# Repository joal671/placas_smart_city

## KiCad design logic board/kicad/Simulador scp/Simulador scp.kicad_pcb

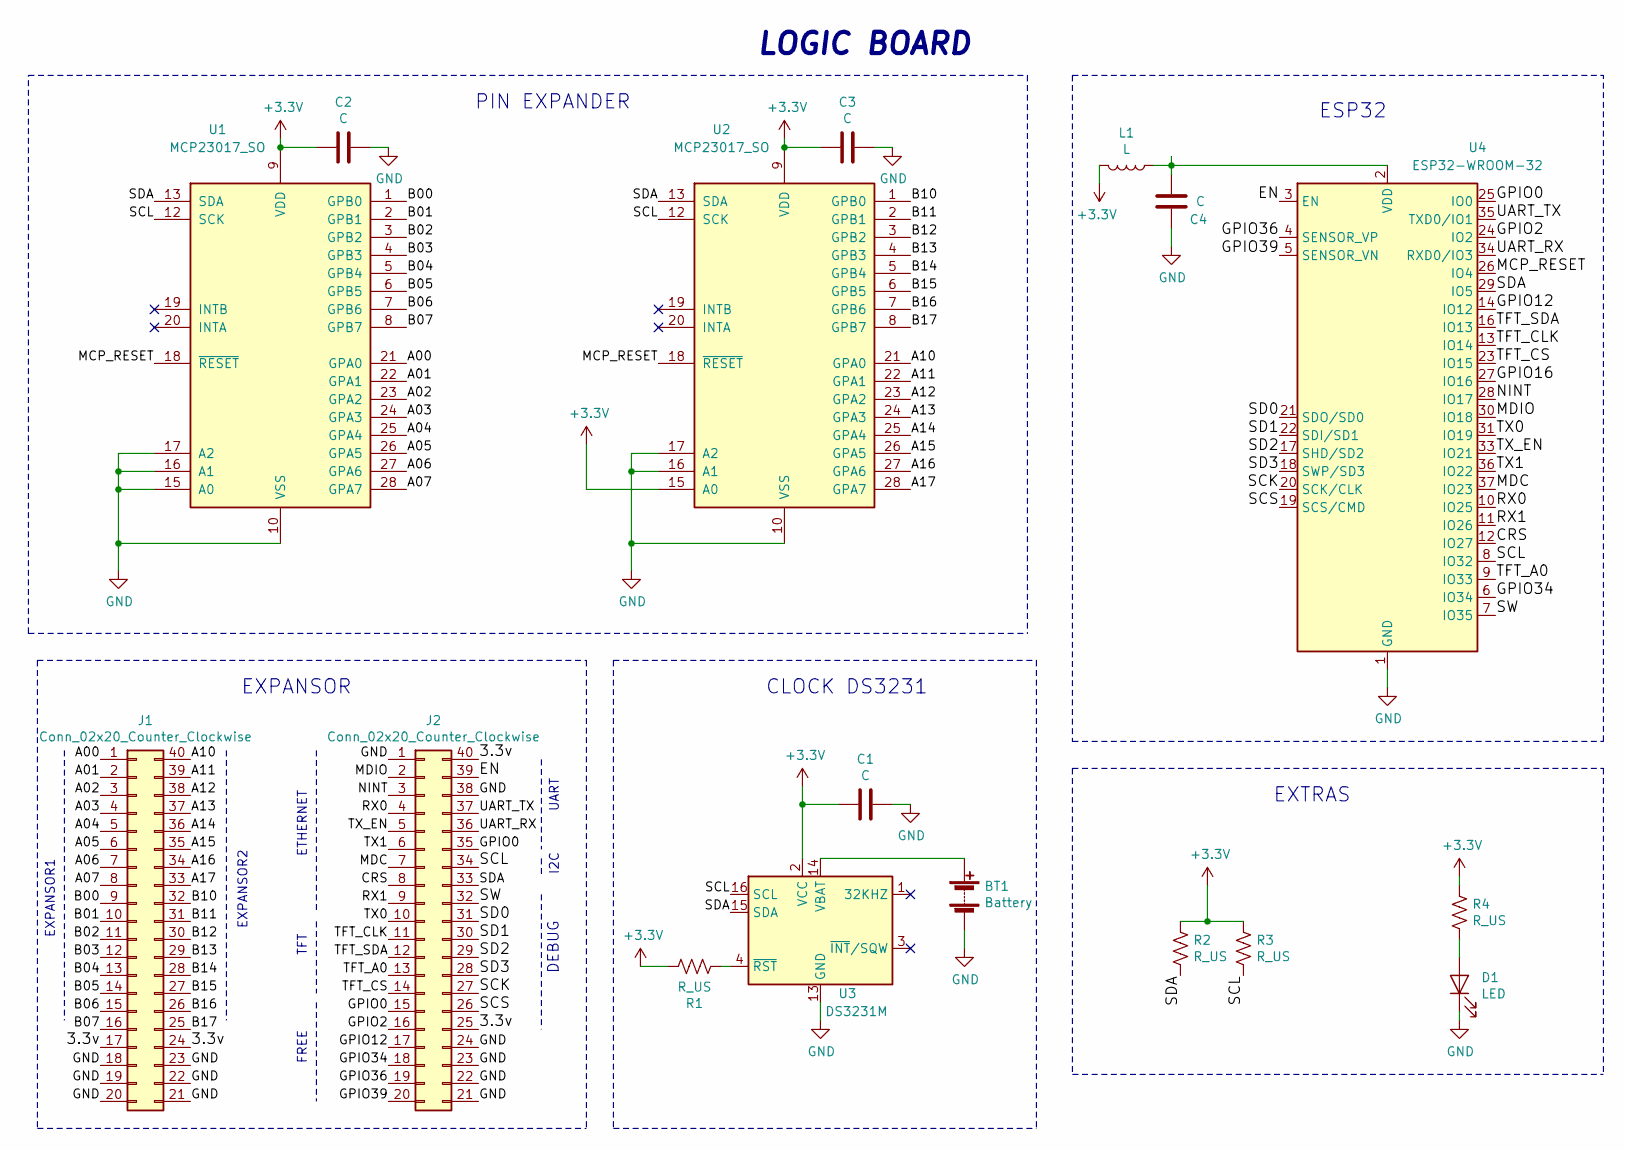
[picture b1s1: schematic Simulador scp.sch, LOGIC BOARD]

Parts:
BT1: Battery; BatteryHolder_Keystone_1060_1x2032
C1, C2, C3, C4: C; C_0805_2012Metric
D1: LED; LED_0805_2012Metric
J1, J2: Conn_02x20_Counter_Clockwise; Header 2x20-2.54mm
L1: L; L_0805_2012Metric
R1, R2, R3, R4: R_US; R_0805_2012Metric
U1, U2: MCP23017_SO; SOIC-28W_7.5x17.9mm_P1.27mm
U3: DS3231M; SOIC-16W_7.5x10.3mm_P1.27mm
U4: ESP32-WROOM-32

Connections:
+3V3: C1.2, C2.2, C3.2, L1.2, R1.1, R2.1, R3.1, R4.1, U1.9 (VDD), U2.9 (VDD), U2.15 (A0), U3.2 (VCC)
/3.3v: J1.17, J1.24, J2.25, J2.40
/A00: J1.1, U1.21 (GPA0)
/A01: J1.2, U1.22 (GPA1)
/A02: J1.3, U1.23 (GPA2)
/A03: J1.4, U1.24 (GPA3)
/A04: J1.5, U1.25 (GPA4)
/A05: J1.6, U1.26 (GPA5)
/A06: J1.7, U1.27 (GPA6)
/A07: J1.8, U1.28 (GPA7)
/A10: J1.40, U2.21 (GPA0)
/A11: J1.39, U2.22 (GPA1)
/A12: J1.38, U2.23 (GPA2)
/A13: J1.37, U2.24 (GPA3)
/A14: J1.36, U2.25 (GPA4)
/A15: J1.35, U2.26 (GPA5)
/A16: J1.34, U2.27 (GPA6)
/A17: J1.33, U2.28 (GPA7)
/B00: J1.9, U1.1 (GPB0)
/B01: J1.10, U1.2 (GPB1)
/B02: J1.11, U1.3 (GPB2)
/B03: J1.12, U1.4 (GPB3)
/B04: J1.13, U1.5 (GPB4)
/B05: J1.14, U1.6 (GPB5)
/B06: J1.15, U1.7 (GPB6)
/B07: J1.16, U1.8 (GPB7)
/B10: J1.32, U2.1 (GPB0)
/B11: J1.31, U2.2 (GPB1)
/B12: J1.30, U2.3 (GPB2)
/B13: J1.29, U2.4 (GPB3)
/B14: J1.28, U2.5 (GPB4)
/B15: J1.27, U2.6 (GPB5)
/B16: J1.26, U2.7 (GPB6)
/B17: J1.25, U2.8 (GPB7)
/CRS: J2.8, U4.12 (IO27)
/EN: J2.39, U4.3 (EN)
/GPIO0: J2.15, J2.35, U4.25 (IO0)
/GPIO2: J2.16, U4.24 (IO2)
/GPIO12: J2.17, U4.14 (IO12)
/GPIO16: U4.27 (IO16)
/GPIO34: J2.18, U4.6 (IO34)
/GPIO36: J2.19, U4.4 (SENSOR_VP)
/GPIO39: J2.20, U4.5 (SENSOR_VN)
/MCP_RESET: U1.18 (~RESET~), U2.18 (~RESET~), U4.26 (IO4)
/MDC: J2.7, U4.37 (IO23)
/MDIO: J2.2, U4.30 (IO18)
/NINT: J2.3, U4.28 (IO17)
/RX0: J2.4, U4.10 (IO25)
/RX1: J2.9, U4.11 (IO26)
/SCK: J2.27, U4.20 (SCK/CLK)
/SCL: J2.34, R3.2, U1.12 (SCK), U2.12 (SCK), U3.16 (SCL), U4.8 (IO32)
/SCS: J2.26, U4.19 (SCS/CMD)
/SD0: J2.31, U4.21 (SDO/SD0)
/SD1: J2.30, U4.22 (SDI/SD1)
/SD2: J2.29, U4.17 (SHD/SD2)
/SD3: J2.28, U4.18 (SWP/SD3)
/SDA: J2.33, R2.2, U1.13 (SDA), U2.13 (SDA), U3.15 (SDA), U4.29 (IO5)
/SW: J2.32, U4.7 (IO35)
/TFT_A0: J2.13, U4.9 (IO33)
/TFT_CLK: J2.11, U4.13 (IO14)
/TFT_CS: J2.14, U4.23 (IO15)
/TFT_SDA: J2.12, U4.16 (IO13)
/TX0: J2.10, U4.31 (IO19)
/TX1: J2.6, U4.36 (IO22)
/TX_EN: J2.5, U4.33 (IO21)
/UART_RX: J2.36, U4.34 (RXD0/IO3)
/UART_TX: J2.37, U4.35 (TXD0/IO1)
GND: BT1.2 (-), C1.1, C2.1, C3.1, C4.1, D1.1 (K), J1.18, J1.19, J1.20, J1.21, J1.22, J1.23, J2.1, J2.21, J2.22, J2.23, J2.24, J2.38, U1.10 (VSS), U1.15 (A0), U1.16 (A1), U1.17 (A2), U2.10 (VSS), U2.16 (A1), U2.17 (A2), U3.5 (GND), U3.6 (GND), U3.7 (GND), U3.8 (GND), U3.9 (GND), U3.10 (GND), U3.11 (GND), U3.12 (GND), U3.13 (GND), U4.1 (GND), U4.15 (GND), U4.38 (GND), U4.39 (GND)
unnamed: BT1.1 (+), U3.14 (VBAT)
unnamed: C4.2, L1.1, U4.2 (VDD)
unnamed: D1.2 (A), R4.2
unnamed: R1.2, U3.4 (~RST)

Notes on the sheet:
PIN EXPANDER
ESP32
EXPANSOR
CLOCK DS3231
EXPANSOR1
EXTRAS
LOGIC BOARD
EXPANSOR2
DEBUG
FREE
UART
TFT
I2C
ETHERNET

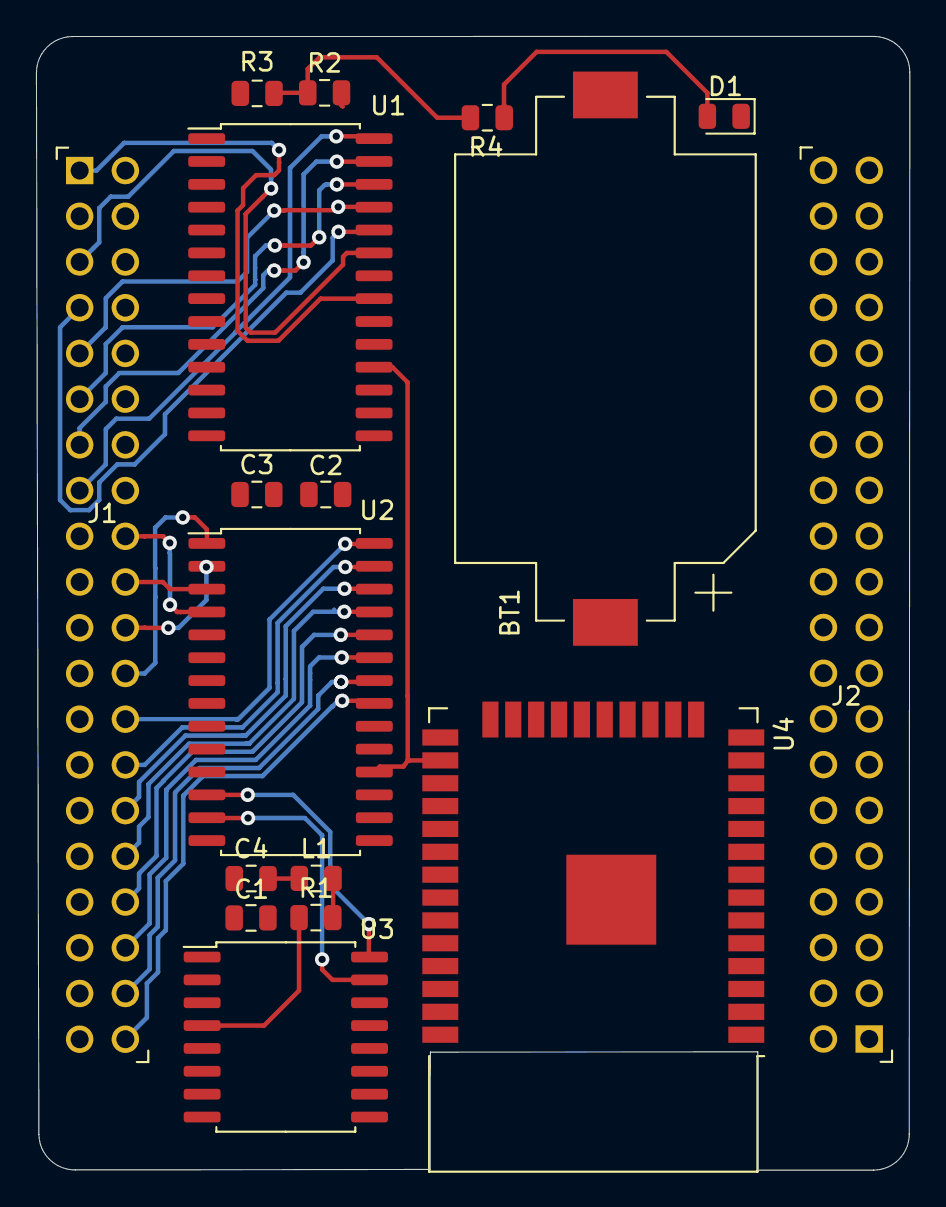
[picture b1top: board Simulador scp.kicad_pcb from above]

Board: 2 copper layers, 48.5 x 63.0 mm, 17 parts (0 on the bottom side), 71 nets.

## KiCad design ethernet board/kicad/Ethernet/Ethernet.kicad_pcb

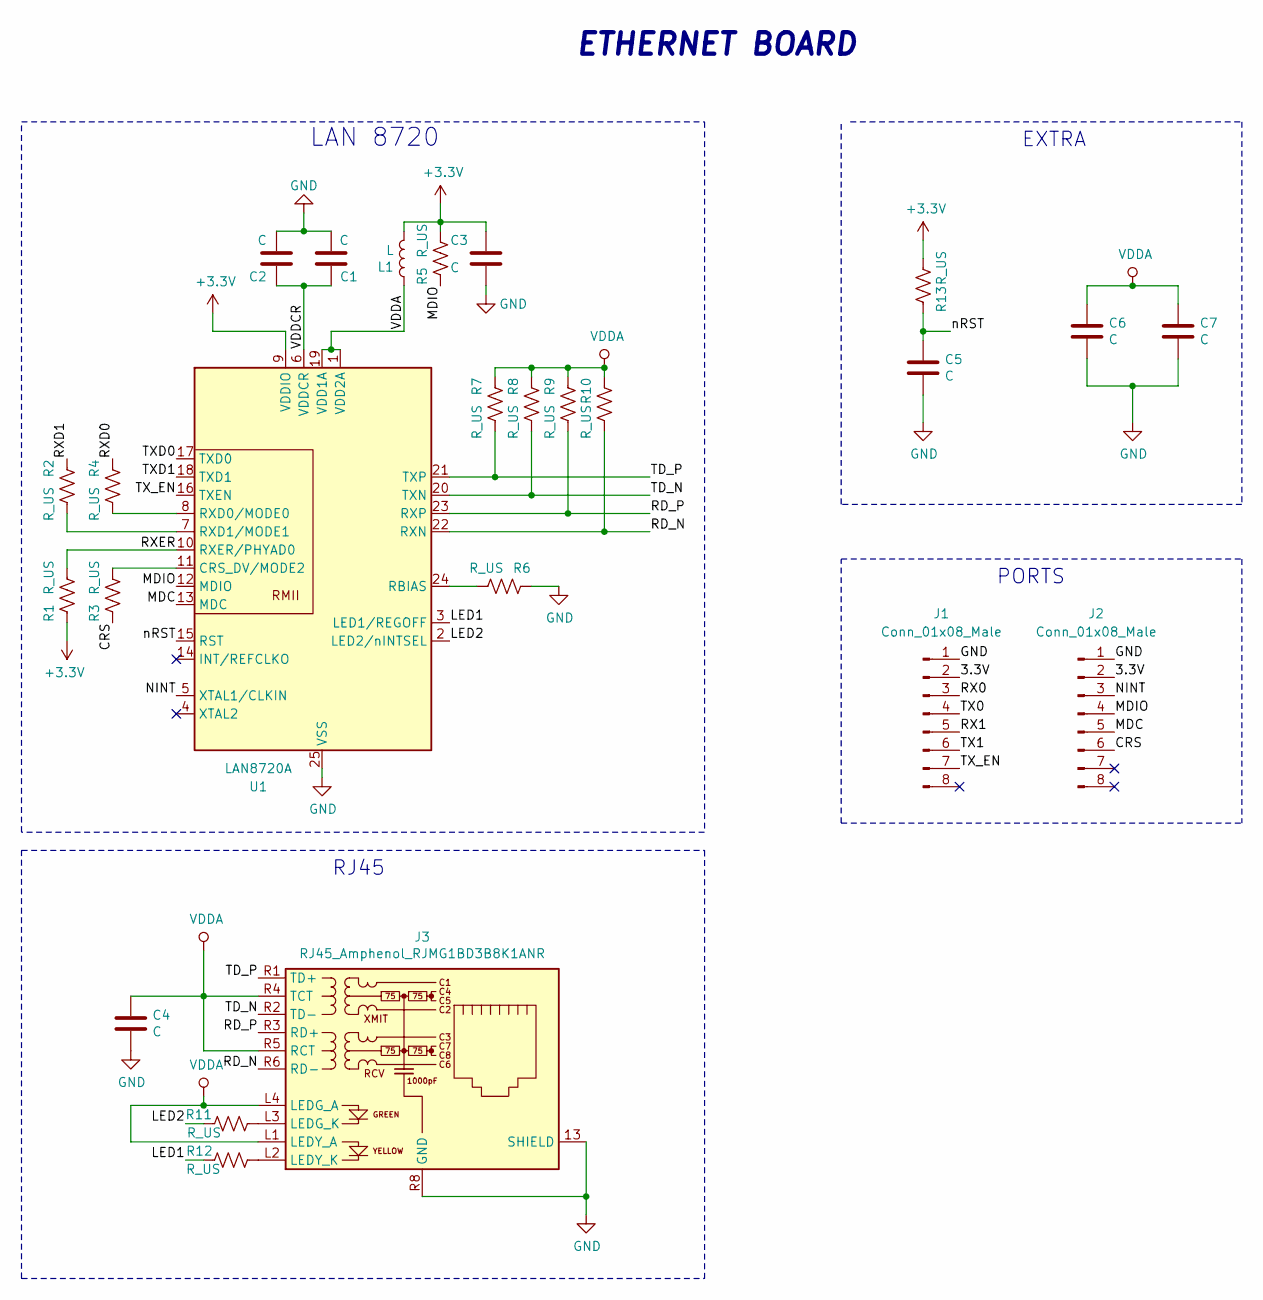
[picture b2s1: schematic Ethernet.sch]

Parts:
C1, C2, C3, C4, C5, C6, C7: C; C_0805_2012Metric
J1, J2: Conn_01x08_Male; PinHeader_1x09_P2.54mm_Vertical
J3: RJ45_Amphenol_RJMG1BD3B8K1ANR
L1: L; L_0805_2012Metric
R1, R2, R3, R4, R5, R6, R7, R8, R9, R10, R11, R12, R13: R_US; R_0805_2012Metric
U1: LAN8720A; QFN-24-1EP_4x4mm_P0.5mm_EP2.6x2.6mm

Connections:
+3V3: C3.1, L1.2, R1.2, R5.1, R13.1, U1.9 (VDDIO)
/3.3V: J1.2, J2.2
/CRS: J2.6, R3.2
/LED1: R12.2, U1.3 (LED1/REGOFF)
/LED2: R11.1, U1.2 (LED2/nINTSEL)
/MDC: J2.5, U1.13 (MDC)
/MDIO: J2.4, R5.2, U1.12 (MDIO)
/NINT: J2.3, U1.5 (XTAL1/CLKIN)
/RD_N: J3.R6 (RD-), R10.1, U1.22 (RXN)
/RD_P: J3.R3 (RD+), R9.1, U1.23 (RXP)
/RX0: J1.3
/RX1: J1.5
/RXD0: R4.2
/RXD1: R2.2
/RXER: R1.1, U1.10 (RXER/PHYAD0)
/TD_N: J3.R2 (TD-), R8.1, U1.20 (TXN)
/TD_P: J3.R1 (TD+), R7.1, U1.21 (TXP)
/TX0: J1.4
/TX1: J1.6
/TXD0: U1.17 (TXD0)
/TXD1: U1.18 (TXD1)
/TX_EN: J1.7, U1.16 (TXEN)
/VDDCR: C1.1, C2.1, U1.6 (VDDCR)
/nRST: C5.1, R13.2, U1.15 (RST)
GND: C1.2, C2.2, C3.2, C4.2, C5.2, C6.2, C7.2, J1.1, J2.1, J3.13 (SHIELD), J3.R8 (GND), R6.2, U1.25 (VSS)
unnamed: J3.L2 (LEDY_K), R12.1
unnamed: J3.L3 (LEDG_K), R11.2
unnamed: R2.1, U1.7 (RXD1/MODE1)
unnamed: R3.1, U1.11 (CRS_DV/MODE2)
unnamed: R4.1, U1.8 (RXD0/MODE0)
unnamed: R6.1, U1.24 (RBIAS)
VDDA: C4.1, C6.1, C7.1, J3.L1 (LEDY_A), J3.L4 (LEDG_A), J3.R4 (TCT), J3.R5 (RCT), L1.1, R7.2, R8.2, R9.2, R10.2, U1.1 (VDD2A), U1.19 (VDD1A)

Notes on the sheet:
ETHERNET BOARD
LAN 8720
EXTRA
RJ45
PORTS

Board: 2 copper layers, 25 parts (0 on the bottom side), 24 nets, no tracks yet.

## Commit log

2020-09-12 primer committ
